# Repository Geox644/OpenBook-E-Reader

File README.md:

# OpenBook Reader
<br>
Proiectul consta in realizarea unui E-Book Reader accesibil, cu un ecran ce imita hartia, special pentru a avea un consum redus de energie, dar si pentru a oferi utilizatorului o excperinta cat mai placuta. Dispozitivul a fost proiectat de la zero: crearea schemei electrice cu componentele hardware, realizarea 2D PCB + procesul de rutare, trecerea in plan 3D.

<br>

## Diagrama Bloc

<br>

## Descriere functionalitati hardware

### ESP32-C6

* Rol: ESP32-C6 este microcontroller-ul, practic creierul dispozitivului care controleaza toate componentele, gestioneaza si datele.
* Arhitectura: RISC-V 32-bit
* Protocoale: GPIO, I2C, UART, SPI,  PWM
* Memorie:  SD + Flash
* Consum: 10mA (idle), 200mA (WiFi activat)

### MAX17048

* Rol: MAX17048 este monitorul bateriei care vede in timp real nivelul bateriei LiPo si procentul de încarcare.
* Protocol: I2C, SCL: IO6, SDA: IO7

### MCP73831

* Rol: Controloeaza incarcarea eficienta acumulatorul LiPo prin port-ul USB.
* Capacitate: ~500 mA

### XC6204

* Rol: XC6204 reprezinta regulator-ul LDO care reduce tensiunea de la 5V la 3.3V pentru alimentarea sigura a componentelor.

### RTC – DS3231

* Rol: Tine ora exacta chiar si fara alimentare, pentru afisarea corecta a timpului.
* Protocol: I2C, SCL: IO6, SDA: IO7
* Consum: 0.15mA

### BME688 SENSOR

* Rol: Masoara temperatura, umiditatea, etc.
* Protocol: I2C, SCL: IO6, SDA: IO7
* Consum: 3.1mA

### Card SD

* Rol: Salvarea datelor pe dispozitiv.
* Protocol: SPI (pini IO18–IO22)
* Consum: 50mA

### W25Q512JV

* Rol: W25Q512JV este memoria Flash care stocheaza resurse statice folosite de sistemul dispozitivului.
* Protocol: SPI (pini IO18–IO21)
* Consum: 25mA

### Butoane

* Rol: Permite interactiunea manuala a utilizatorului cu dispozitivul.
* Exista 3 tipuri de butoane (Reset, Boot, Change)
* Protocol: GPIO

### E-INK DISPLAY

* Rol: Afisarea continutului/informatiilor de pe dispozitiv. Are un consum redus, deoarece foloseste putine semnale, curentul este necesar atunci cand imaginea se schimba si ramane afisata fara alimentare continua.
* Protocol: GPIO, SPI
* Consum: 40mA

  <br>

## Interfete si pinii de comunicare

| Componente | Interfete | Pini ESP32-C6 |
|-----------|--------------|-----------|
| I2C | BME688, RTC, Battery | SDA (IO22), SCL (IO21) |
| SPI | SD Card, E-paper, NOR Flash | SCK (IO6), MOSI (IO7), MISO (IO2) |
| GPIO | Buttons | IO0 - IO23 |
| USB | Conectare alte dispozitive / incarcare | USB_D+/D- (IO13/IO12) |

<br>

## Observatii

* Modelul 3D al TP-urilor a fost realizat manual de catre mine si au fost pizitionate pe marginea placutei, cat mai aproape de componentele cu care aveau lagaturi
* Au fost facute modificari de footprint pentru U4 – MAX17048G+T10, deoarece alimentarea VBAT a fost proiectata cu o latime de 0.3mm, iar footprint-ul avea o latime a pinilor de 0.27mm.
* Componentele, dimensiunile si pozitiile acestora respecta cat de mult se poate design-ul de referinta.
* ~140 vias PCB
  
<br>

## Bill Of Materials (BOM)

| Componenta | Link | Datasheet |
|-----------|--------------|-----------|
| CAPACITOR 0402 | [Model](https://componentsearchengine.com/part-view/CC0402MRX5R5BB106/YAGEO) | [Datasheet](https://componentsearchengine.com/Datasheets/2/CC0402MRX5R5BB106.pdf) |
| Capacitor 0805| [Model](https://ro.mouser.com/ProductDetail/KYOCERA-AVX/SD0805S020S1R0?qs=jCA%252BPfw4LHbpkAoSnwrdjw%3D%3D) | [Datasheet](https://ro.mouser.com/datasheet/2/40/schottky-3165252.pdf) |
| CPH3225A | [Model](https://www.snapeda.com/parts/CPH3225A/Seiko+Instruments/view-part/?ref=eda) | [Datasheet](https://www.snapeda.com/parts/CPH3225A/Seiko+Instruments/view-part/?ref=eda) |
| RCL CPOL 3528 | [Model](https://www.snapeda.com/parts/TAJB475K025RNJ/AVX/view-part/?ref=dk&t=capacitor%203528&con_ref=None) | [Datasheet](https://s3.amazonaws.com/snapeda/datasheet/TAJB475K025RNJ_AVX.pdf) |
| Resistor 0402 | [Model](https://componentsearchengine.com/part-view/R0402%201%25%20100%20K%20(RC0402FR-07100KL)/YAGEO) | [Datasheet](https://www.yageo.com/upload/media/product/products/datasheet/rchip/PYu-RC_Group_51_RoHS_L_12.pdf) |
| MBR0530 DIODE | [Model](https://eu.mouser.com/ProductDetail/KYOCERA-AVX/SD0805S020S1R0?qs=jCA%252BPfw4LHbpkAoSnwrdjw%3D%3D) | [Datasheet](https://ro.mouser.com/datasheet/2/40/schottky-3165252.pdf) |
| PGB1010603MR DIODE | [Model](https://www.snapeda.com/parts/PGB1010603MR/Littelfuse/view-part/?ref=eda) | [Datasheet](https://www.snapeda.com/parts/PGB1010603MR/Littelfuse%20Inc./datasheet/) |
| BUTTON | [Model](https://industry.panasonic.com/global/en/products/control/switch/light-touch/number/evqpuj02k) | [Datasheet](https://industry.panasonic.com/global/en/downloads?tab=catalog&small_g_cd=203&part_no=EVQPUJ02K) |
| LED 0603 | [Model](https://www.snapeda.com/parts/KP-1608SURCK/Kingbright/view-part/?ref=search&t=LED%200603) | [Datasheet](https://www.snapeda.com/parts/KP-1608SURCK/Kingbright/datasheet/) |
| BME680 Sensor | [Model](https://www.digikey.ro/en/models/7401317) | [Datasheet](https://www.bosch-sensortec.com/media/boschsensortec/downloads/datasheets/bst-bme680-ds001.pdf) |
| SJ | [Model](https://grabcad.com/library/solder-jumpers-1) | [Datasheet](https://grabcad.com/library/solder-jumpers-1) |
| ESP32C6 Varistor 1812 (PFMF) | [Model](https://ro.mouser.com/ProductDetail/EPCOS-TDK/B72520T0350K062?qs=dEfas%2FXlABIszF52uu7vrg%3D%3D) | [Datasheet](https://www.snapeda.com/parts/RC0603JR-070RL/Yageo/datasheet/) |
| FH34SRJ-24S-0.5SH (J1) | [Model](https://www.snapeda.com/parts/FH34SRJ-24S-0.5SH(99)/Hirose/view-part/) | [Datasheet](https://www.snapeda.com/parts/FH34SRJ-24S-0.5SH(99)/Hirose%20Connector/datasheet/) |
| USB4110-GF-A (J2) | [Model](https://componentsearchengine.com/part-view/USB4110-GF-A/GCT%20(GLOBAL%20CONNECTOR%20TECHNOLOGY)) | [Datasheet](https://gct.co/files/drawings/usb4110.pdf) |
| QWIIC Connector (J3) | [Model](https://www.snapeda.com/parts/PRT-14417/SparkFun/view-part/) | [Datasheet](https://www.snapeda.com/parts/PRT-14417/SparkFun%20Electronics/datasheet/) |
| 112A-TAAR-R03 (J4)| [Model](https://www.snapeda.com/parts/112A-TAAR-R03/Attend/view-part/) | [Datasheet](https://www.snapeda.com/parts/112A-TAAR-R03/Attend/datasheet/) |
| 744043680 (L1)| [Model](https://ro.mouser.com/ProductDetail/Wurth-Elektronik/744043680?qs=PGXP4M47uW6VkZq%252BkzjrHA%3D%3D) | [Datasheet](https://www.we-online.com/components/products/datasheet/744043680.pdf) |
| DMG2305UX-7 (Q1&Q2) | [Model](https://componentsearchengine.com/part-view/DMG2305UX-7/Diodes%20Incorporated) | [Datasheet](https://www.snapeda.com/parts/SI1308EDL-T1-GE3/Vishay%20Siliconix/datasheet/) |
| SI1308EDL-T1-GE3 (Q3) | [Model](https://componentsearchengine.com/part-view/SI1308EDL-T1-GE3/Vishay) | [Datasheet](https://www.snapeda.com/parts/SI1308EDL-T1-GE3/Vishay%20Siliconix/datasheet/) |
| W25Q512JVEIQ (U1) | [Model](https://www.snapeda.com/parts/W25Q512JVEIQ/Winbond+Electronics/view-part/?ref=eda) | [Datasheet](https://www.winbond.com/resource-files/W25Q512JV%20SPI%20RevB%2006252019%20KMS.pdf) |
| ESP32C6 WROOM-1-N8 (U2) | [Model](https://www.snapeda.com/parts/ESP32-C6-WROOM-1-N8/Espressif+Systems/view-part/?ref=eda) | [Datasheet](https://www.snapeda.com/parts/ESP32-C6-WROOM-1-N8/Espressif+Systems/view-part/?ref=eda) |
| DS3231SN (U3) | [Model](https://www.snapeda.com/parts/DS3231SN%23/Analog+Devices/view-part/?ref=eda) | [Datasheet](https://www.snapeda.com/parts/DS3231SN%23/Analog%20Devices/datasheet/) |
| MAX17048G+T10 (U4) | [Model](https://www.snapeda.com/parts/MAX17048G+T10/Analog+Devices/view-part/?ref=eda) | [Datasheet](https://www.snapeda.com/parts/MAX17048G+T10/Analog%20Devices/datasheet/) |
| MCP73831 Power Management (U5) | [Model](https://www.snapeda.com/parts/MCP73831T-2ACI/OT/Microchip/view-part/) | [Datasheet](https://www.snapeda.com/parts/MCP73831T-2ACI/OT/Microchip/datasheet/) |
| BD5229G-TR (IC1) | [Model](https://www.digikey.ee/en/models/658502) | [Datasheet](https://fscdn.rohm.com/en/products/databook/datasheet/ic/power/voltage_detector/bd52xxg-e.pdf) |
| XC6220A331MR-G (IC4) | [Model](https://componentsearchengine.com/part-view/XC6220A331MR-G/Torex) | [Datasheet](https://product.torexsemi.com/system/files/series/xc6220.pdf) |

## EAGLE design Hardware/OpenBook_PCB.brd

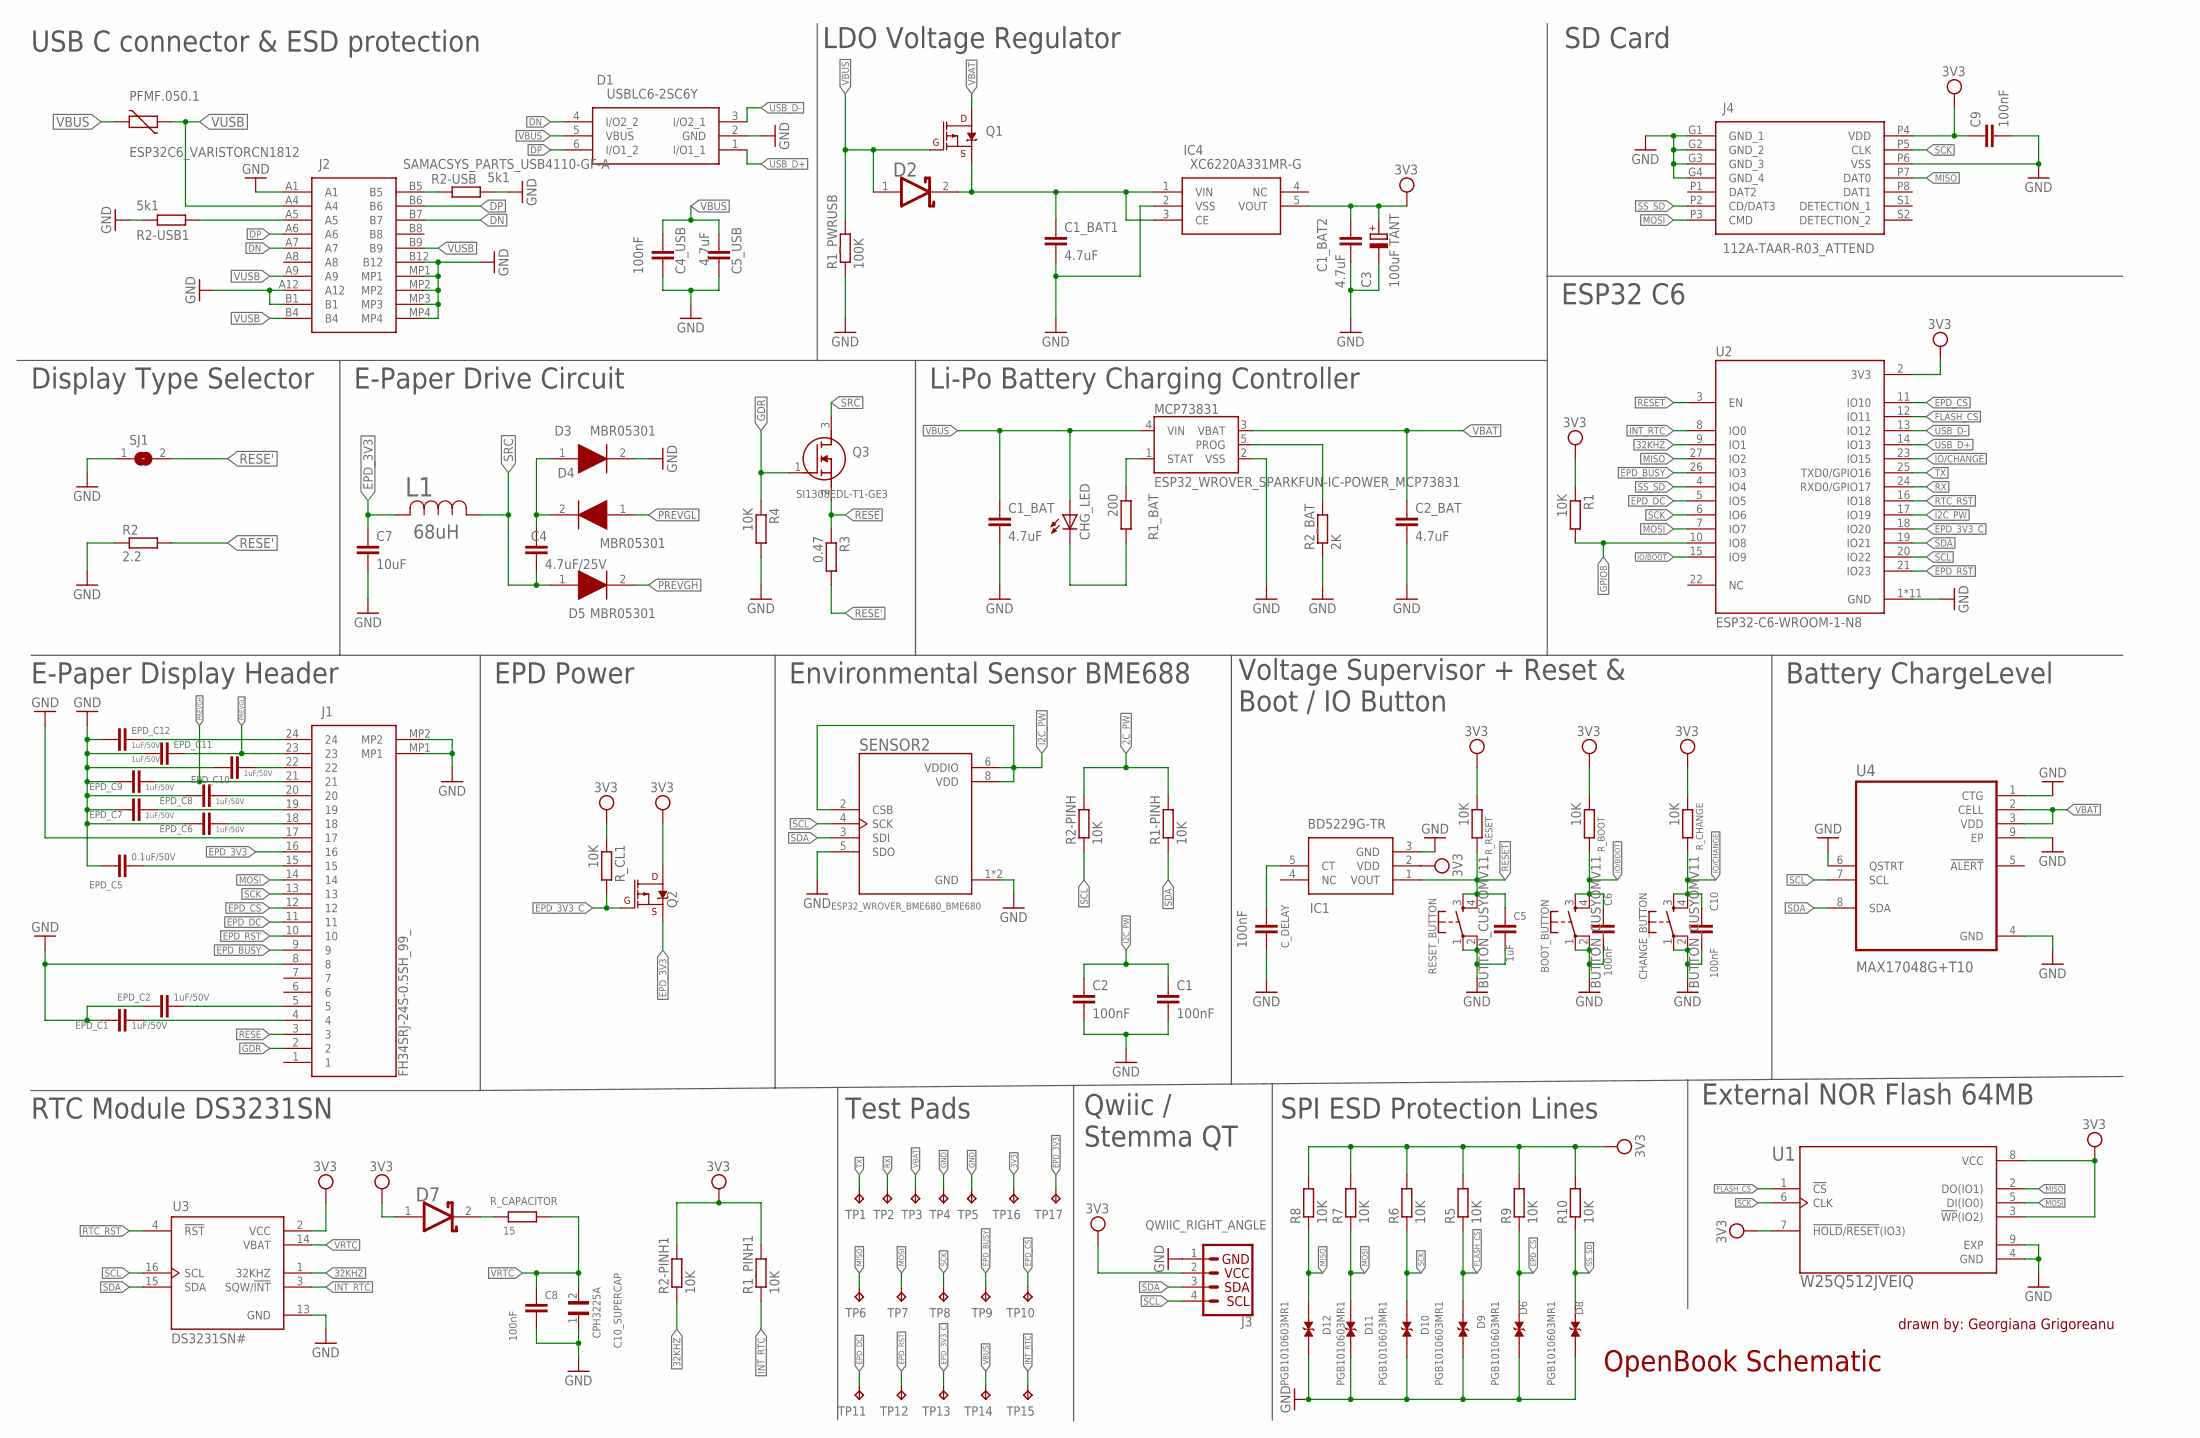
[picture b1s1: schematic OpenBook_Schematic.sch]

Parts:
BOOT_BUTTON: BUTTON_CUSYOMV11; MYBUTTON
C1, C2, C4_USB, C6, C8, C9, C10: 100nF; ESP32_WROVER_EAGLE-LTSPICE_C0402
C1_BAT, C1_BAT1, C1_BAT2, C2_BAT, C5_USB: 4.7uF; ESP32_WROVER_EAGLE-LTSPICE_C0402
C3: 100uF TANT; RCL_CT3528
C4: 4.7uF/25V; ESP32_WROVER_EAGLE-LTSPICE_C0402
C5: 1uF; ESP32_WROVER_EAGLE-LTSPICE_C0402
C7: 10uF; ESP32_WROVER_EAGLE-LTSPICE_C0402
C10_SUPERCAP: CPH3225A; CAPCP3225X100N
CHANGE_BUTTON: BUTTON_CUSYOMV11; MYBUTTON
CHG_LED: ADAFRUIT_LEDCHIP-LED0603; ADAFRUIT_CHIP-LED0603
C_DELAY: 100nF; ESP32_WROVER_EAGLE-LTSPICE_C0402
D1: USBLC6-2SC6Y; SOT95P280X145-6N
D2, D7: ESP32_WROVER_AVX---SD0805S020S1R0_AVX_SD0805S020S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; ESP32_WROVER_AVX---SD0805S020S1R0_AVX_SD0805S020S1R0_0
D3, D4, D5: MBR05301; SOD3716X135N
D6, D8, D9, D10, D11, D12: PGB1010603MR1; DIOC1608X36N
EPD_C1, EPD_C2, EPD_C6, EPD_C7, EPD_C8, EPD_C9, EPD_C10, EPD_C11, EPD_C12: 1uF/50V; ESP32_WROVER_EAGLE-LTSPICE_C0402
EPD_C5: 0.1uF/50V; ESP32_WROVER_EAGLE-LTSPICE_C0402
IC1: BD5229G-TR; SOT95P280X125-5N
IC4: XC6220A331MR-G; SOT95P280X120-5N
J1: FH34SRJ-24S-0.5SH_99_; FH34SRJ24S05SH99
J2: SAMACSYS_PARTS_USB4110-GF-A; SAMACSYS_PARTS_USB4110GFA
J3: QWIIC_RIGHT_ANGLE; JST04_1MM_RA
J4: 112A-TAAR-R03_ATTEND; 112ATAARR03ATTEND
L1: 68uH; IND_4828-WE-TPC_WRE
MCP73831: ESP32_WROVER_SPARKFUN-IC-POWER_MCP73831; ESP32_WROVER_SPARKFUN-IC-POWER_SOT23-5
PFMF.050.1: ESP32C6_VARISTORCN1812; ESP32C6_VARISTOR_CT/CN1812
Q1, Q2: 20V/4.2A/52mΩ/1.4W; ESP32_WROVER_SPARKFUN-DISCRETESEMI_SOT23-3
Q3: SI1308EDL-T1-GE3; SOT65P210X110-3N
R1, R1-PINH, R1_PINH1, R2-PINH, R2-PINH1, R4, R5, R6, R7, R8, R9, R10: 10K; ESP32_WROVER_EAGLE-LTSPICE_C0402
R1_BAT: 200; ESP32_WROVER_EAGLE-LTSPICE_C0402
R1_PWRUSB: 100K; ESP32_WROVER_EAGLE-LTSPICE_C0402
R2: 2.2; ESP32_WROVER_EAGLE-LTSPICE_C0402
R2-USB, R2-USB1: 5k1; ESP32_WROVER_EAGLE-LTSPICE_C0402
R2_BAT: 2K; ESP32_WROVER_EAGLE-LTSPICE_C0402
R3: 0.47; ESP32_WROVER_EAGLE-LTSPICE_C0402
RESET_BUTTON: BUTTON_CUSYOMV11; MYBUTTON
R_BOOT: 10K; ESP32_WROVER_EAGLE-LTSPICE_C0402
R_CAPACITOR: 15; ESP32_WROVER_EAGLE-LTSPICE_C0402
R_CHANGE: 10K; ESP32_WROVER_EAGLE-LTSPICE_C0402
R_CL1: 10K; ESP32_WROVER_EAGLE-LTSPICE_C0402
R_RESET: 10K; ESP32_WROVER_EAGLE-LTSPICE_C0402
SENSOR2: ESP32_WROVER_BME680_BME680; ESP32_WROVER_BME680_PSON80P300X300X100-8N
SJ1: SJ
TP1, TP2, TP3, TP4, TP5, TP6, TP7, TP8, TP9, TP10, TP11, TP12, TP13, TP14, TP15, TP16, TP17: TP; TP20R
U1: W25Q512JVEIQ; SON127P600X800X80-9N
U2: ESP32-C6-WROOM-1-N8; XCVR_ESP32-C6-WROOM-1-N8
U3: DS3231SN#; SOIC127P1032X265-16N
U4: MAX17048G+T10; SON50P200X200X80-9N

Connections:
2C_PW: R1-PINH.2, R2-PINH.2
3V3: C1_BAT2.1, C3.+, C9.1, D7.1 (ANODE), IC1.2 (VDD), IC4.5 (VOUT), J3.2, J4.P4 (VDD), Q2.1 (D), R1.1, R1_PINH1.2, R2-PINH1.2, R5.2, R6.2, R7.2, R8.2, R9.2, R10.2, R_BOOT.1, R_CHANGE.1, R_CL1.1, R_RESET.1, TP16.TP, U1.3 (!WP!(IO2)), U1.7 (!HOLD!/!RESET!(IO3)), U1.8 (VCC), U2.2 (3V3), U3.2 (VCC)
32KHZ: R2-PINH1.1, U2.9 (IO1), U3.1 (32KHZ)
DN: D1.4 (I/O2_2), J2.A7, J2.B7
DP: D1.6 (I/O1_2), J2.A6, J2.B6
EPD_3V3: C7.1, J1.16, L1.2, Q2.3 (S), TP17.TP
EPD_3V3_C: Q2.2 (G), R_CL1.2, TP13.TP, U2.18 (IO20)
EPD_BUSY: J1.9, TP9.TP, U2.26 (IO3)
EPD_CS: D6.1, J1.12, R9.1, TP10.TP, U2.11 (IO10)
EPD_DC: J1.11, TP11.TP, U2.5 (IO5)
EPD_RST: J1.10, TP12.TP, U2.21 (IO23)
FLASH_CS: D9.1, R5.1, U1.1 (!CS), U2.12 (IO11)
GDR: J1.2, Q3.1 (G), R4.1
GND: BOOT_BUTTON.1, BOOT_BUTTON.2, C1.2, C1_BAT.2, C1_BAT1.2, C1_BAT2.2, C2.2, C2_BAT.2, C3.-, C4_USB.2, C5.2, C5_USB.2, C6.2, C7.2, C8.2, C9.2, C10.2, C10_SUPERCAP.1, CHANGE_BUTTON.1, CHANGE_BUTTON.2, C_DELAY.2, D1.2 (GND), D3.2 (K), D6.2, D8.2, D9.2, D10.2, D11.2, D12.2, EPD_C1.2, EPD_C2.2, EPD_C5.2, EPD_C6.2, EPD_C7.2, EPD_C8.2, EPD_C9.2, EPD_C10.2, EPD_C11.2, EPD_C12.2, IC1.3 (GND), IC4.2 (VSS), J1.8, J1.17, J1.MP1, J1.MP2, J2.A1, J2.A12, J2.B1, J2.B12, J2.MP1, J2.MP2, J2.MP3, J2.MP4, J3.1, J4.G1 (GND_1), J4.G2 (GND_2), J4.G3 (GND_3), J4.G4 (GND_4), J4.P6 (VSS), MCP73831.2 (VSS), R1_PWRUSB.1, R2.1, R2-USB.2, R2-USB1.1, R2_BAT.1, R4.2, RESET_BUTTON.1, RESET_BUTTON.2, SENSOR2.1 (GND), SENSOR2.5 (SDO), SENSOR2.7 (GND), SJ1.1, TP4.TP, TP5.TP, U1.4 (GND), U1.9 (EXP), U2.1 (GND), U2.28 (GND), U2.29_1 (GND), U2.29_2 (GND), U2.29_3 (GND), U2.29_4 (GND), U2.29_5 (GND), U2.29_6 (GND), U2.29_7 (GND), U2.29_8 (GND), U2.29_9 (GND), U3.13 (GND), U4.1 (CTG), U4.4 (GND), U4.6 (QSTRT), U4.9 (EP)
GPIO8: R1.2, U2.10 (IO8)
I2C_PW: C1.1, C2.1, SENSOR2.2 (CSB), SENSOR2.6 (VDDIO), SENSOR2.8 (VDD), U2.17 (IO19)
INT_RTC: R1_PINH1.1, TP15.TP, U2.8 (IO0), U3.3 (SQW/!INT)
IO/BOOT: BOOT_BUTTON.3, BOOT_BUTTON.4, C6.1, R_BOOT.2, U2.15 (IO9)
IO/CHANGE: C10.1, CHANGE_BUTTON.3, CHANGE_BUTTON.4, R_CHANGE.2, U2.23 (IO15)
MISO: D12.1, J4.P7 (DAT0), R8.1, TP6.TP, U1.2 (DO(IO1)), U2.27 (IO2)
MOSI: D11.1, J1.14, J4.P3 (CMD), R7.1, TP7.TP, U1.5 (DI(IO0)), U2.7 (IO7)
unnamed: J2.A5, R2-USB1.2
unnamed: J2.B5, R2-USB.1
unnamed: C1_BAT1.1, D2.2 (CATHODE), IC4.1 (VIN), IC4.3 (CE), Q1.3 (S)
unnamed: MCP73831.1 (STAT), R1_BAT.1
unnamed: CHG_LED.C, R1_BAT.2
unnamed: C4.1, D3.1 (A), D4.2 (K)
unnamed: EPD_C12.1, J1.24
unnamed: MCP73831.5 (PROG), R2_BAT.2
unnamed: EPD_C6.1, J1.18
unnamed: EPD_C7.1, J1.19
unnamed: EPD_C8.1, J1.20
unnamed: C_DELAY.1, IC1.5 (CT)
unnamed: EPD_C10.1, J1.22
unnamed: D7.2 (CATHODE), R_CAPACITOR.2
unnamed: EPD_C5.1, J1.15
unnamed: EPD_C2.1, J1.5
unnamed: EPD_C1.1, J1.4
PREVGH: D5.2 (K), EPD_C9.1, J1.21
PREVGL: D4.1 (A), EPD_C11.1, J1.23
RESE: J1.3, Q3.2 (S), R3.1
RESE': R2.2, R3.2, SJ1.2
RESET: C5.1, IC1.1 (VOUT), RESET_BUTTON.3, RESET_BUTTON.4, R_RESET.2, U2.3 (EN)
RTC_RST: U2.16 (IO18), U3.4 (!RST)
RX: TP2.TP, U2.24 (RXD0/GPIO17)
SCK: D10.1, J1.13, J4.P5 (CLK), R6.1, TP8.TP, U1.6 (CLK), U2.6 (IO6)
SCL: J3.4, R2-PINH.1, SENSOR2.4 (SCK), U2.20 (IO22), U3.16 (SCL), U4.7 (SCL)
SDA: J3.3, R1-PINH.1, SENSOR2.3 (SDI), U2.19 (IO21), U3.15 (SDA), U4.8 (SDA)
SRC: C4.2, D5.1 (A), L1.1, Q3.3 (D)
SS_SD: D8.1, J4.P2 (CD/DAT3), R10.1, U2.4 (IO4)
TX: TP1.TP, U2.25 (TXD0/GPIO16)
USB_D+: D1.1 (I/O1_1), U2.14 (IO13)
USB_D-: D1.3 (I/O2_1), U2.13 (IO12)
VBAT: C2_BAT.1, MCP73831.3 (VBAT), Q1.1 (D), TP3.TP, U4.2 (CELL), U4.3 (VDD)
VBUS: C1_BAT.1, C4_USB.1, C5_USB.1, CHG_LED.A, D1.5 (VBUS), D2.1 (ANODE), MCP73831.4 (VIN), PFMF.050.1.2, Q1.2 (G), R1_PWRUSB.2, TP14.TP
VRTC: C8.1, C10_SUPERCAP.2, R_CAPACITOR.1, U3.14 (VBAT)
VUSB: J2.A4, J2.A9, J2.B4, J2.B9, PFMF.050.1.1

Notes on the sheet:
USB C connector & ESD protection
LDO Voltage Regulator
SD Card
E-Paper Drive Circuit
Display Type Selector
Li-Po Battery Charging Controller
ESP32 C6
E-Paper Display Header
EPD Power
Environmental Sensor BME688
Voltage Supervisor + Reset & Boot / IO Button
Battery ChargeLevel
RTC Module DS3231SN
Test Pads
Qwiic / Stemma QT
SPI ESD Protection Lines
External NOR Flash 64MB
OpenBook Schematic
drawn by: Georgiana Grigoreanu

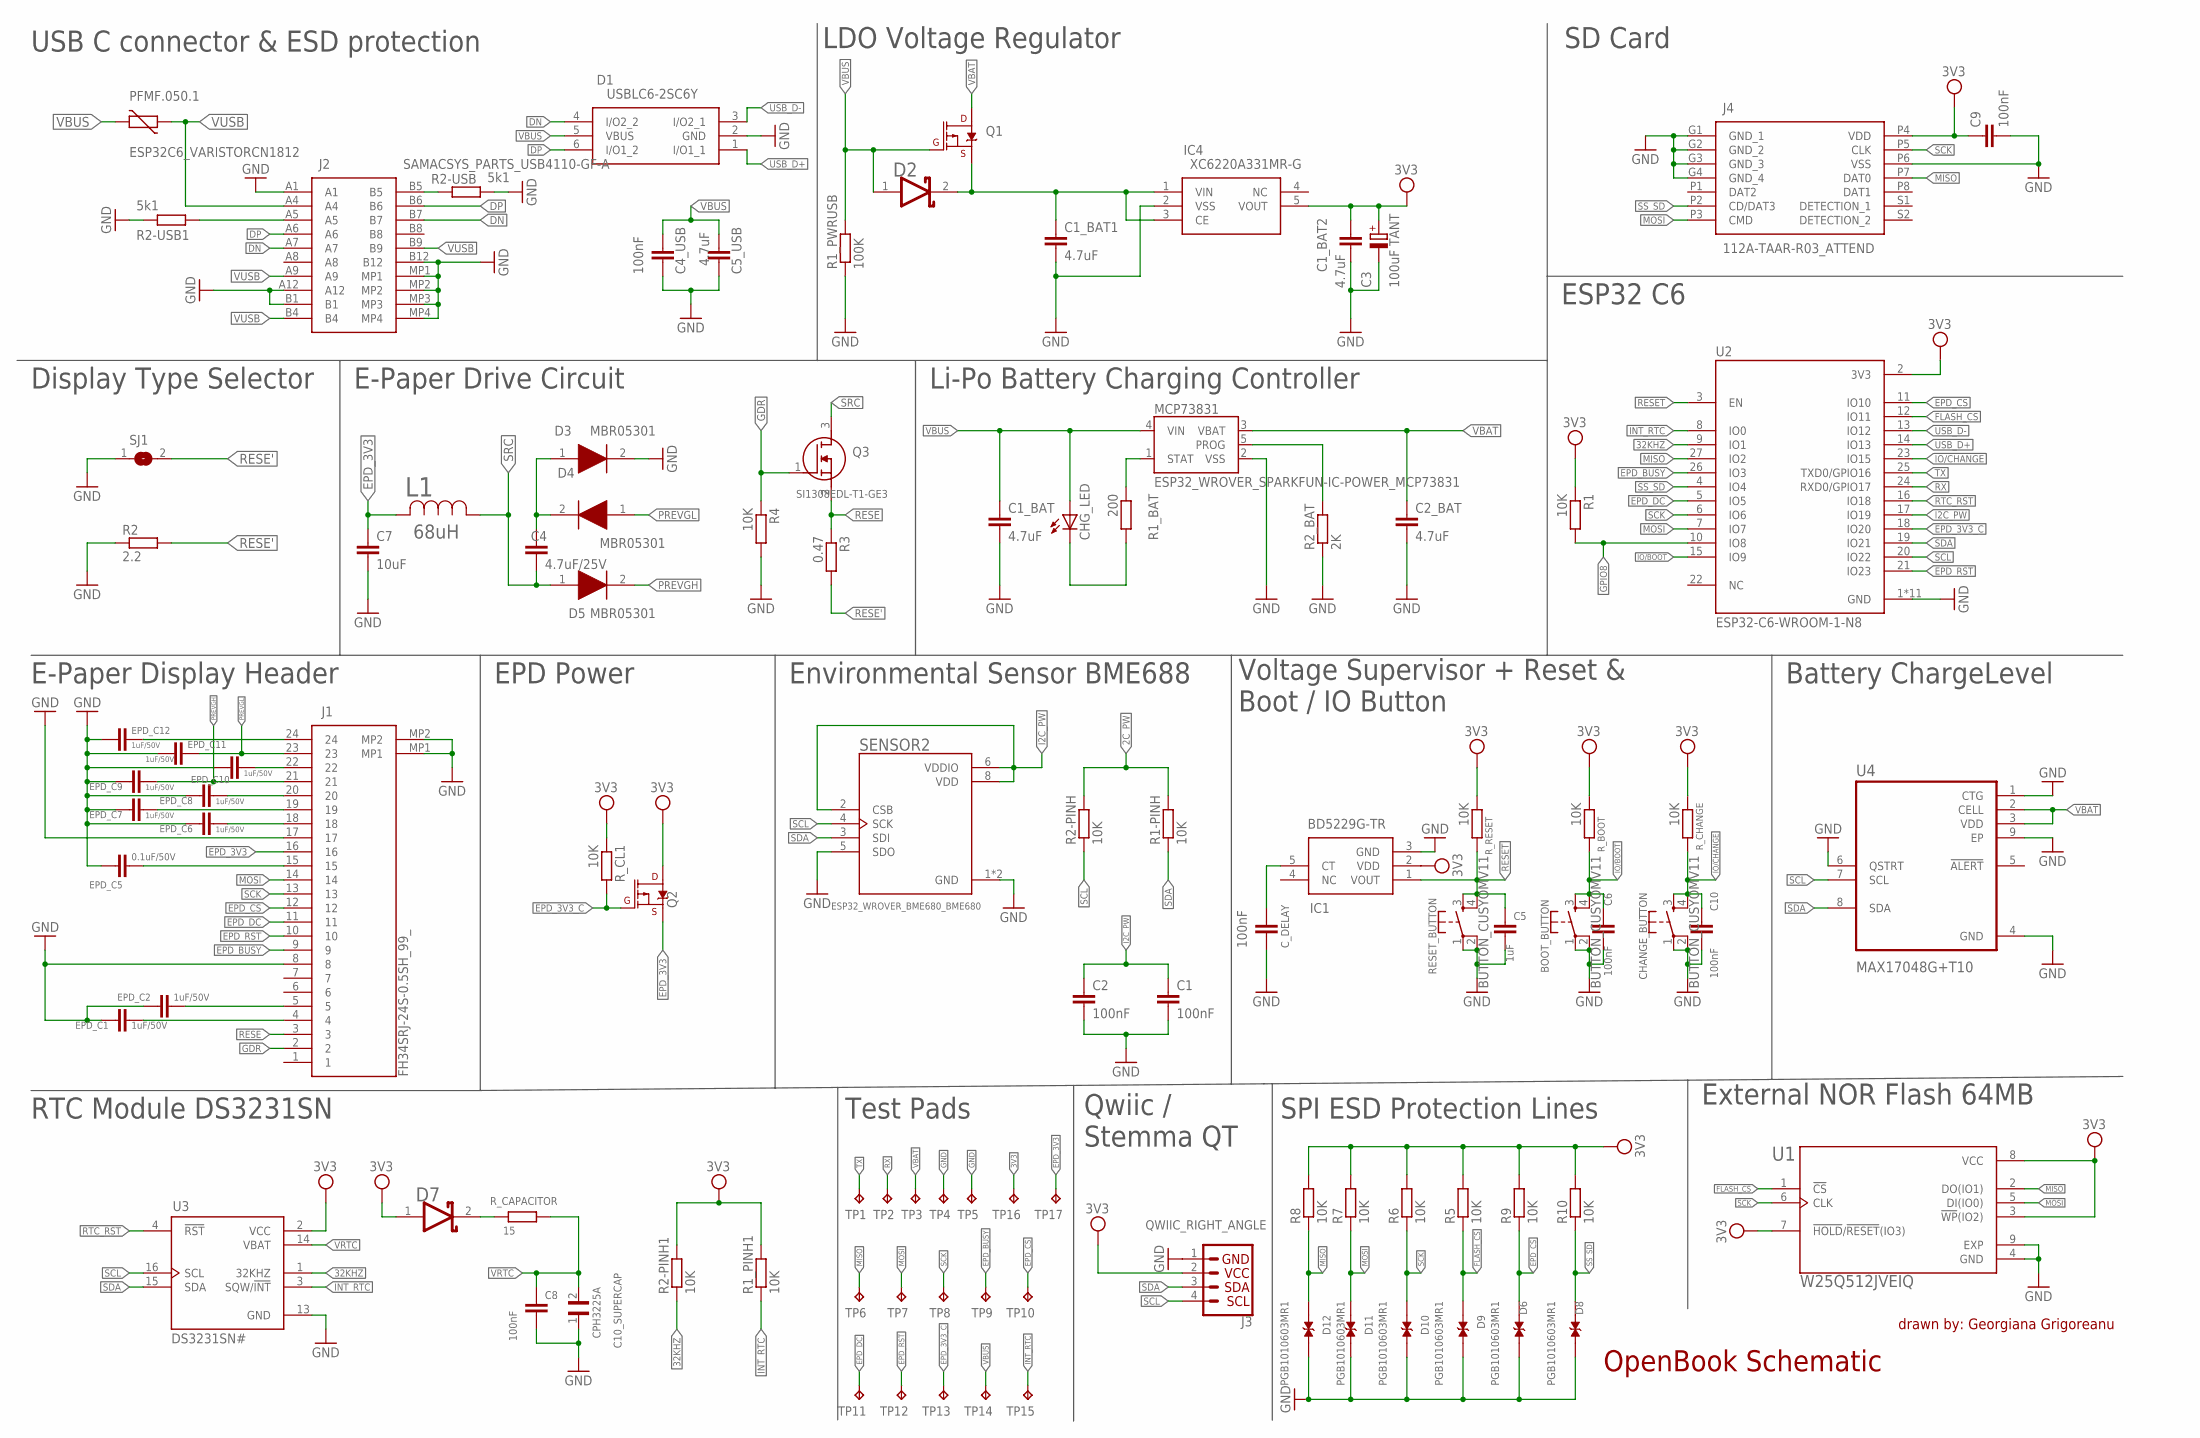
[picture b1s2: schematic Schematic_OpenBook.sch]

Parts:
BOOT_BUTTON: BUTTON_CUSYOMV11; MYBUTTON
C1, C2, C4_USB, C6, C8, C9, C10: 100nF; ESP32_WROVER_EAGLE-LTSPICE_C0402
C1_BAT, C1_BAT1, C1_BAT2, C2_BAT, C5_USB: 4.7uF; ESP32_WROVER_EAGLE-LTSPICE_C0402
C3: 100uF TANT; RCL_CT3528
C4: 4.7uF/25V; ESP32_WROVER_EAGLE-LTSPICE_C0402
C5: 1uF; ESP32_WROVER_EAGLE-LTSPICE_C0402
C7: 10uF; ESP32_WROVER_EAGLE-LTSPICE_C0402
C10_SUPERCAP: CPH3225A; CAPCP3225X100N
CHANGE_BUTTON: BUTTON_CUSYOMV11; MYBUTTON
CHG_LED: ADAFRUIT_LEDCHIP-LED0603; ADAFRUIT_CHIP-LED0603
C_DELAY: 100nF; ESP32_WROVER_EAGLE-LTSPICE_C0402
D1: USBLC6-2SC6Y; SOT95P280X145-6N
D2, D7: ESP32_WROVER_AVX---SD0805S020S1R0_AVX_SD0805S020S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; ESP32_WROVER_AVX---SD0805S020S1R0_AVX_SD0805S020S1R0_0
D3, D4, D5: MBR05301; SOD3716X135N
D6, D8, D9, D10, D11, D12: PGB1010603MR1; DIOC1608X36N
EPD_C1, EPD_C2, EPD_C6, EPD_C7, EPD_C8, EPD_C9, EPD_C10, EPD_C11, EPD_C12: 1uF/50V; ESP32_WROVER_EAGLE-LTSPICE_C0402
EPD_C5: 0.1uF/50V; ESP32_WROVER_EAGLE-LTSPICE_C0402
IC1: BD5229G-TR; SOT95P280X125-5N
IC4: XC6220A331MR-G; SOT95P280X120-5N
J1: FH34SRJ-24S-0.5SH_99_; FH34SRJ24S05SH99
J2: SAMACSYS_PARTS_USB4110-GF-A; SAMACSYS_PARTS_USB4110GFA
J3: QWIIC_RIGHT_ANGLE; JST04_1MM_RA
J4: 112A-TAAR-R03_ATTEND; 112ATAARR03ATTEND
L1: 68uH; IND_4828-WE-TPC_WRE
MCP73831: ESP32_WROVER_SPARKFUN-IC-POWER_MCP73831; ESP32_WROVER_SPARKFUN-IC-POWER_SOT23-5
PFMF.050.1: ESP32C6_VARISTORCN1812; ESP32C6_VARISTOR_CT/CN1812
Q1, Q2: 20V/4.2A/52mΩ/1.4W; ESP32_WROVER_SPARKFUN-DISCRETESEMI_SOT23-3
Q3: SI1308EDL-T1-GE3; SOT65P210X110-3N
R1, R1-PINH, R1_PINH1, R2-PINH, R2-PINH1, R4, R5, R6, R7, R8, R9, R10: 10K; ESP32_WROVER_EAGLE-LTSPICE_C0402
R1_BAT: 200; ESP32_WROVER_EAGLE-LTSPICE_C0402
R1_PWRUSB: 100K; ESP32_WROVER_EAGLE-LTSPICE_C0402
R2: 2.2; ESP32_WROVER_EAGLE-LTSPICE_C0402
R2-USB, R2-USB1: 5k1; ESP32_WROVER_EAGLE-LTSPICE_C0402
R2_BAT: 2K; ESP32_WROVER_EAGLE-LTSPICE_C0402
R3: 0.47; ESP32_WROVER_EAGLE-LTSPICE_C0402
RESET_BUTTON: BUTTON_CUSYOMV11; MYBUTTON
R_BOOT: 10K; ESP32_WROVER_EAGLE-LTSPICE_C0402
R_CAPACITOR: 15; ESP32_WROVER_EAGLE-LTSPICE_C0402
R_CHANGE: 10K; ESP32_WROVER_EAGLE-LTSPICE_C0402
R_CL1: 10K; ESP32_WROVER_EAGLE-LTSPICE_C0402
R_RESET: 10K; ESP32_WROVER_EAGLE-LTSPICE_C0402
SENSOR2: ESP32_WROVER_BME680_BME680; ESP32_WROVER_BME680_PSON80P300X300X100-8N
SJ1: SJ
TP1, TP2, TP3, TP4, TP5, TP6, TP7, TP8, TP9, TP10, TP11, TP12, TP13, TP14, TP15, TP16, TP17: TP; TP20R
U1: W25Q512JVEIQ; SON127P600X800X80-9N
U2: ESP32-C6-WROOM-1-N8; XCVR_ESP32-C6-WROOM-1-N8
U3: DS3231SN#; SOIC127P1032X265-16N
U4: MAX17048G+T10; SON50P200X200X80-9N

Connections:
2C_PW: R1-PINH.2, R2-PINH.2
3V3: C1_BAT2.1, C3.+, C9.1, D7.1 (ANODE), IC1.2 (VDD), IC4.5 (VOUT), J3.2, J4.P4 (VDD), Q2.1 (D), R1.1, R1_PINH1.2, R2-PINH1.2, R5.2, R6.2, R7.2, R8.2, R9.2, R10.2, R_BOOT.1, R_CHANGE.1, R_CL1.1, R_RESET.1, TP16.TP, U1.3 (!WP!(IO2)), U1.7 (!HOLD!/!RESET!(IO3)), U1.8 (VCC), U2.2 (3V3), U3.2 (VCC)
32KHZ: R2-PINH1.1, U2.9 (IO1), U3.1 (32KHZ)
DN: D1.4 (I/O2_2), J2.A7, J2.B7
DP: D1.6 (I/O1_2), J2.A6, J2.B6
EPD_3V3: C7.1, J1.16, L1.2, Q2.3 (S), TP17.TP
EPD_3V3_C: Q2.2 (G), R_CL1.2, TP13.TP, U2.18 (IO20)
EPD_BUSY: J1.9, TP9.TP, U2.26 (IO3)
EPD_CS: D6.1, J1.12, R9.1, TP10.TP, U2.11 (IO10)
EPD_DC: J1.11, TP11.TP, U2.5 (IO5)
EPD_RST: J1.10, TP12.TP, U2.21 (IO23)
FLASH_CS: D9.1, R5.1, U1.1 (!CS), U2.12 (IO11)
GDR: J1.2, Q3.1 (G), R4.1
GND: BOOT_BUTTON.1, BOOT_BUTTON.2, C1.2, C1_BAT.2, C1_BAT1.2, C1_BAT2.2, C2.2, C2_BAT.2, C3.-, C4_USB.2, C5.2, C5_USB.2, C6.2, C7.2, C8.2, C9.2, C10.2, C10_SUPERCAP.1, CHANGE_BUTTON.1, CHANGE_BUTTON.2, C_DELAY.2, D1.2 (GND), D3.2 (K), D6.2, D8.2, D9.2, D10.2, D11.2, D12.2, EPD_C1.2, EPD_C2.2, EPD_C5.2, EPD_C6.2, EPD_C7.2, EPD_C8.2, EPD_C9.2, EPD_C10.2, EPD_C11.2, EPD_C12.2, IC1.3 (GND), IC4.2 (VSS), J1.8, J1.17, J1.MP1, J1.MP2, J2.A1, J2.A12, J2.B1, J2.B12, J2.MP1, J2.MP2, J2.MP3, J2.MP4, J3.1, J4.G1 (GND_1), J4.G2 (GND_2), J4.G3 (GND_3), J4.G4 (GND_4), J4.P6 (VSS), MCP73831.2 (VSS), R1_PWRUSB.1, R2.1, R2-USB.2, R2-USB1.1, R2_BAT.1, R4.2, RESET_BUTTON.1, RESET_BUTTON.2, SENSOR2.1 (GND), SENSOR2.5 (SDO), SENSOR2.7 (GND), SJ1.1, TP4.TP, TP5.TP, U1.4 (GND), U1.9 (EXP), U2.1 (GND), U2.28 (GND), U2.29_1 (GND), U2.29_2 (GND), U2.29_3 (GND), U2.29_4 (GND), U2.29_5 (GND), U2.29_6 (GND), U2.29_7 (GND), U2.29_8 (GND), U2.29_9 (GND), U3.13 (GND), U4.1 (CTG), U4.4 (GND), U4.6 (QSTRT), U4.9 (EP)
GPIO8: R1.2, U2.10 (IO8)
I2C_PW: C1.1, C2.1, SENSOR2.2 (CSB), SENSOR2.6 (VDDIO), SENSOR2.8 (VDD), U2.17 (IO19)
INT_RTC: R1_PINH1.1, TP15.TP, U2.8 (IO0), U3.3 (SQW/!INT)
IO/BOOT: BOOT_BUTTON.3, BOOT_BUTTON.4, C6.1, R_BOOT.2, U2.15 (IO9)
IO/CHANGE: C10.1, CHANGE_BUTTON.3, CHANGE_BUTTON.4, R_CHANGE.2, U2.23 (IO15)
MISO: D12.1, J4.P7 (DAT0), R8.1, TP6.TP, U1.2 (DO(IO1)), U2.27 (IO2)
MOSI: D11.1, J1.14, J4.P3 (CMD), R7.1, TP7.TP, U1.5 (DI(IO0)), U2.7 (IO7)
unnamed: J2.A5, R2-USB1.2
unnamed: J2.B5, R2-USB.1
unnamed: C1_BAT1.1, D2.2 (CATHODE), IC4.1 (VIN), IC4.3 (CE), Q1.3 (S)
unnamed: MCP73831.1 (STAT), R1_BAT.1
unnamed: CHG_LED.C, R1_BAT.2
unnamed: C4.1, D3.1 (A), D4.2 (K)
unnamed: EPD_C12.1, J1.24
unnamed: MCP73831.5 (PROG), R2_BAT.2
unnamed: EPD_C6.1, J1.18
unnamed: EPD_C7.1, J1.19
unnamed: EPD_C8.1, J1.20
unnamed: C_DELAY.1, IC1.5 (CT)
unnamed: EPD_C10.1, J1.22
unnamed: D7.2 (CATHODE), R_CAPACITOR.2
unnamed: EPD_C5.1, J1.15
unnamed: EPD_C2.1, J1.5
unnamed: EPD_C1.1, J1.4
PREVGH: D5.2 (K), EPD_C9.1, J1.21
PREVGL: D4.1 (A), EPD_C11.1, J1.23
RESE: J1.3, Q3.2 (S), R3.1
RESE': R2.2, R3.2, SJ1.2
RESET: C5.1, IC1.1 (VOUT), RESET_BUTTON.3, RESET_BUTTON.4, R_RESET.2, U2.3 (EN)
RTC_RST: U2.16 (IO18), U3.4 (!RST)
RX: TP2.TP, U2.24 (RXD0/GPIO17)
SCK: D10.1, J1.13, J4.P5 (CLK), R6.1, TP8.TP, U1.6 (CLK), U2.6 (IO6)
SCL: J3.4, R2-PINH.1, SENSOR2.4 (SCK), U2.20 (IO22), U3.16 (SCL), U4.7 (SCL)
SDA: J3.3, R1-PINH.1, SENSOR2.3 (SDI), U2.19 (IO21), U3.15 (SDA), U4.8 (SDA)
SRC: C4.2, D5.1 (A), L1.1, Q3.3 (D)
SS_SD: D8.1, J4.P2 (CD/DAT3), R10.1, U2.4 (IO4)
TX: TP1.TP, U2.25 (TXD0/GPIO16)
USB_D+: D1.1 (I/O1_1), U2.14 (IO13)
USB_D-: D1.3 (I/O2_1), U2.13 (IO12)
VBAT: C2_BAT.1, MCP73831.3 (VBAT), Q1.1 (D), TP3.TP, U4.2 (CELL), U4.3 (VDD)
VBUS: C1_BAT.1, C4_USB.1, C5_USB.1, CHG_LED.A, D1.5 (VBUS), D2.1 (ANODE), MCP73831.4 (VIN), PFMF.050.1.2, Q1.2 (G), R1_PWRUSB.2, TP14.TP
VRTC: C8.1, C10_SUPERCAP.2, R_CAPACITOR.1, U3.14 (VBAT)
VUSB: J2.A4, J2.A9, J2.B4, J2.B9, PFMF.050.1.1

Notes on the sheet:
USB C connector & ESD protection
LDO Voltage Regulator
SD Card
E-Paper Drive Circuit
Display Type Selector
Li-Po Battery Charging Controller
ESP32 C6
E-Paper Display Header
EPD Power
Environmental Sensor BME688
Voltage Supervisor + Reset & Boot / IO Button
Battery ChargeLevel
RTC Module DS3231SN
Test Pads
Qwiic / Stemma QT
SPI ESD Protection Lines
External NOR Flash 64MB
OpenBook Schematic
drawn by: Georgiana Grigoreanu

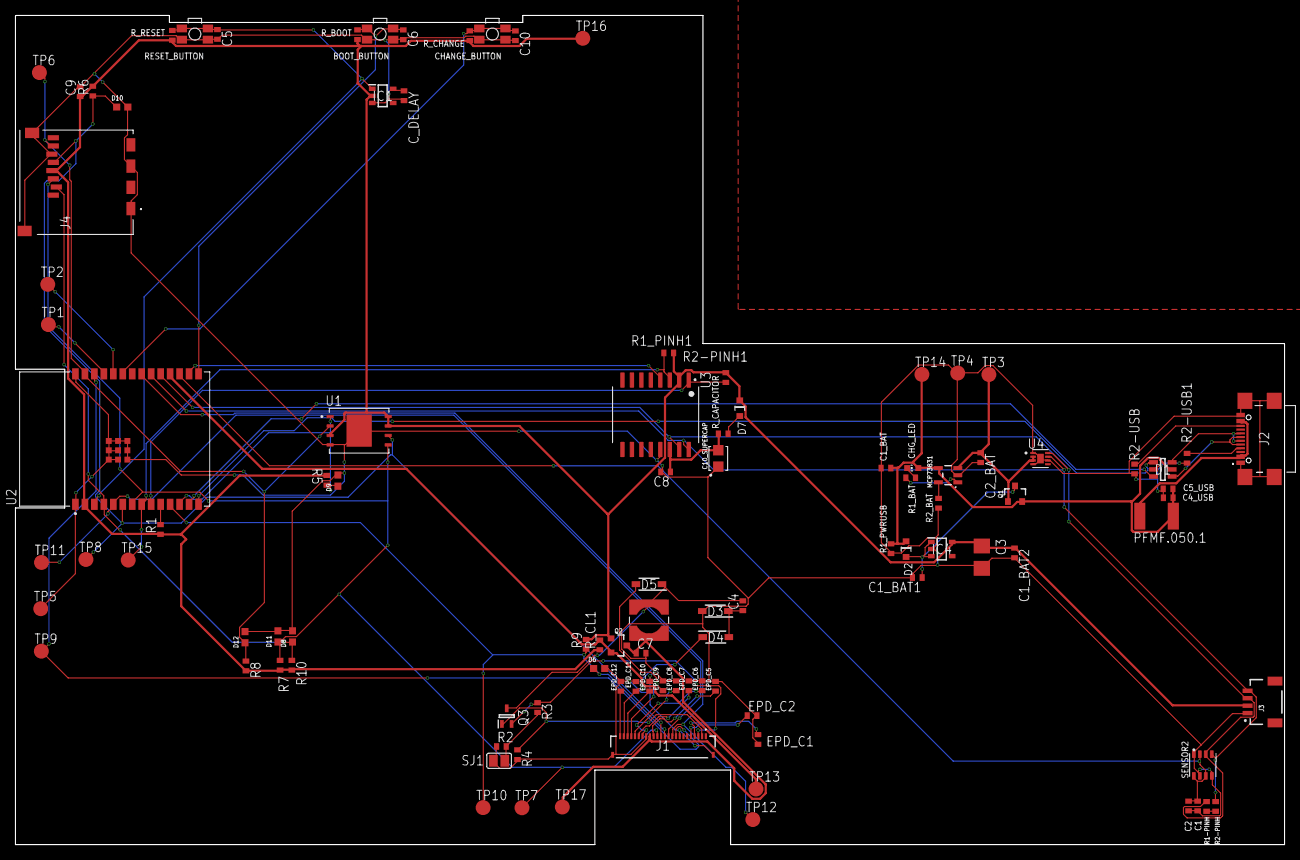
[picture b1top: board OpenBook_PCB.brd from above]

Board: 2 copper layers, 170.2 x 111.2 mm, 103 parts (0 on the bottom side), 57 nets.

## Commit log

2025-04-05 Create LICENSE
2025-04-15 fixed issues

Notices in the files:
parts and their libraries:
COPYRIGHT: Copyright (C) 2024 Ultra Librarian. All rights reserved.
